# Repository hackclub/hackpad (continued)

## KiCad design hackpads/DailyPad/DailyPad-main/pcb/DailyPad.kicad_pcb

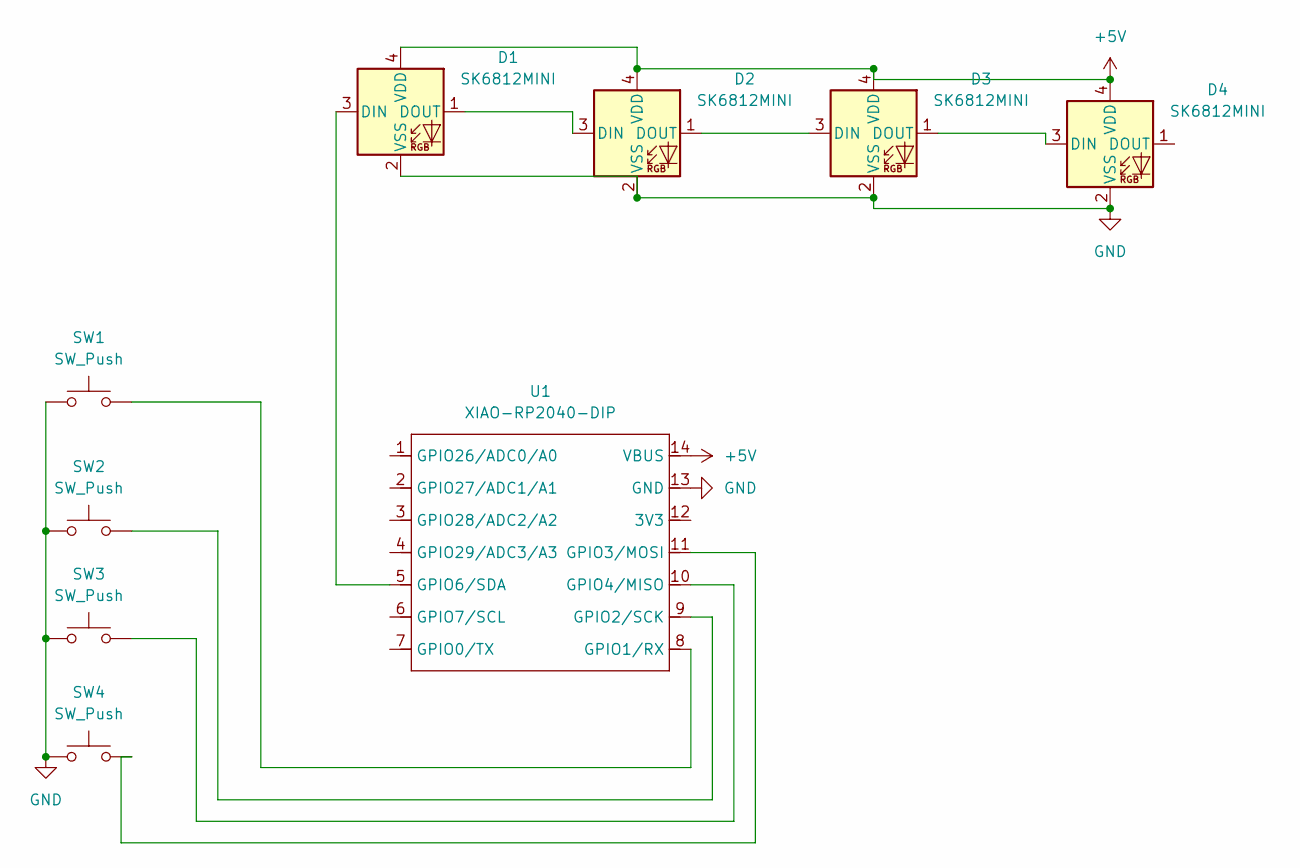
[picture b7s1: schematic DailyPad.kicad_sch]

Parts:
D1, D2, D3, D4: SK6812MINI; LED_SK6812MINI_PLCC4_3.5x3.5mm_P1.75mm
SW1, SW2, SW3, SW4: SW_Push; SW_Cherry_MX_1.00u_PCB
U1: XIAO-RP2040-DIP

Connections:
+5V: D1.4 (VDD), D2.4 (VDD), D3.4 (VDD), D4.4 (VDD), U1.14 (VBUS)
GND: D1.2 (VSS), D2.2 (VSS), D3.2 (VSS), D4.2 (VSS), SW1.1, SW2.1, SW3.1, SW4.1, U1.13 (GND)
unnamed: D1.3 (DIN), U1.5 (GPIO6/SDA)
unnamed: D1.1 (DOUT), D2.3 (DIN)
unnamed: D2.1 (DOUT), D3.3 (DIN)
unnamed: D3.1 (DOUT), D4.3 (DIN)
unnamed: SW1.2, U1.8 (GPIO1/RX)
unnamed: SW2.2, U1.9 (GPIO2/SCK)
unnamed: SW4.2, U1.11 (GPIO3/MOSI)
unnamed: SW3.2, U1.10 (GPIO4/MISO)

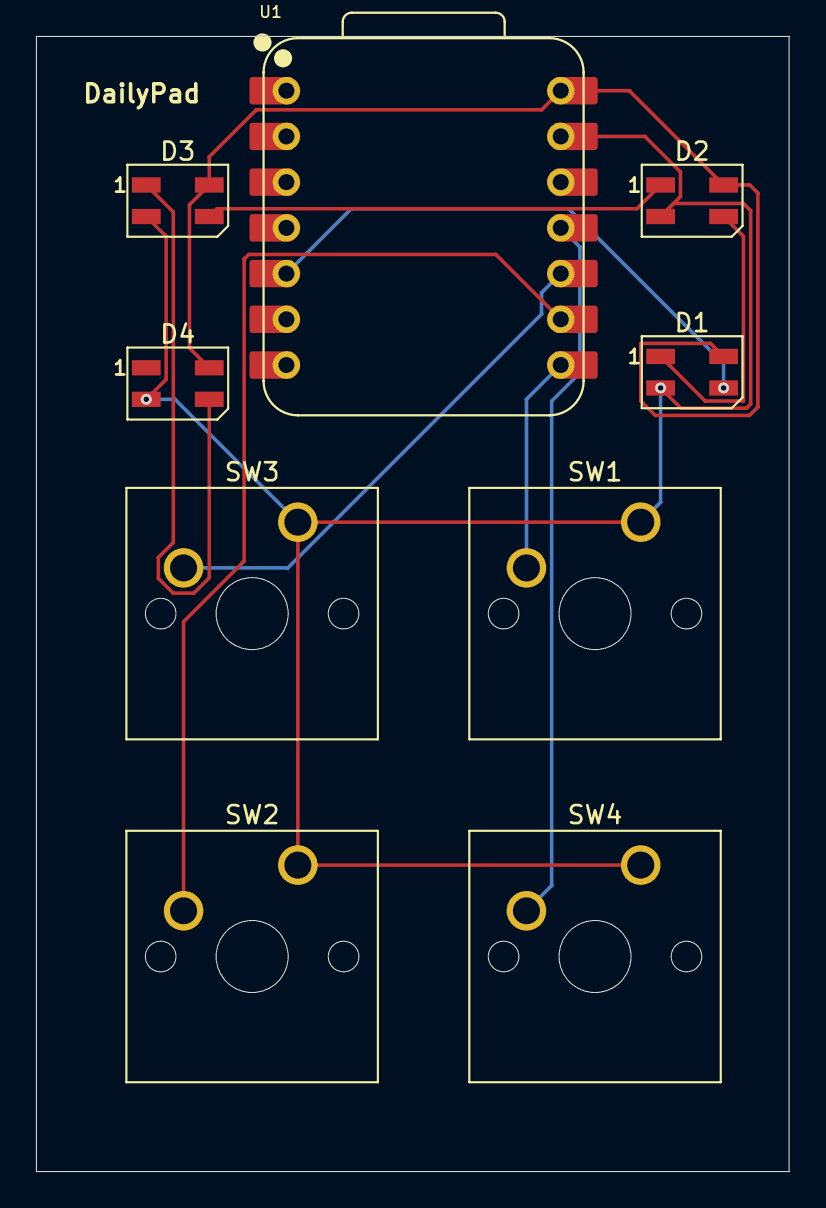
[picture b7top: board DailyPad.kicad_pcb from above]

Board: 2 copper layers, 41.8 x 63.1 mm, 9 parts (0 on the bottom side), 10 nets.
